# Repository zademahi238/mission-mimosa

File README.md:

# Mission Mimosa

### A Visuo-Tactile Manipulation System

*Giving robots a sense of touch.*

---

## Overview

**Mission Mimosa** explores **visuo-tactile manipulation** on the **SO-101 robotic arm**, combining visual observations with tactile sensing for robot manipulation.

The main objective is to investigate:

> **Does tactile information improve robot manipulation performance?**

To answer this, we compare **task-completion success rates with and without tactile sensing** across different robot-learning policies.

---

## Components

### SO-101

The **SO-101** robotic arm is used as the primary platform for collecting demonstrations and evaluating learned manipulation policies.

### FlexiTac

**FlexiTac** provides the tactile sensing hardware used to capture contact information during manipulation.

→ [`flexitac/`](./flexitac)

### LeFlexiTac

**LeFlexiTac** integrates tactile sensing with the **LeRobot** framework, enabling tactile observations to be incorporated into robot-learning workflows.

→ [`leflexitac/`](./leflexitac)

### LeRobot

**LeRobot** provides the robotics framework used for data collection, policy training, and deployment on the SO-101.

→ [`lerobot/`](./lerobot)

---

## Policies

Mission Mimosa explores multiple approaches for learning robot manipulation:

* **[ACT](./docs/policies/act.md)** — Action Chunking with Transformers for learning robot actions from demonstrations.

* **[B-Spline Policy](./docs/imitation-learning/bspline_policy_updated.md)** — Represents robot actions as smooth, continuous trajectories for manipulation.

* **[Diffusion Policy](./docs/policies/diffusion.md)** — Uses diffusion-based action generation for visuomotor control.

* **[SmolVLA](https://huggingface.co/blog/smolvla)** — A compact Vision-Language-Action model designed for efficient real-world robotic manipulation. SmolVLA-450M combines a vision-language model with a flow-matching action expert and is designed to run on relatively affordable hardware, including the SO-101.

Comparing these policies allows us to study how different learning approaches perform with visual information alone and when tactile information is introduced.

---

## Experiment

The core experiment compares two observation settings:

| Setup                | Vision | Tactile |
| :------------------- | :----: | :-----: |
| **Vision Only**      |    ✓   |    —    |
| **Vision + Tactile** |    ✓   |    ✓    |

Each setup is evaluated using **task-completion success rate** across manipulation tasks and different learning policies.

```chart Success Rate Comparison
[
  {
    "label": "ACT",
    "bars": [
      { "label": "50 eps", "value": 80, "series": "Vision" },
      { "label": "50 eps", "value": 90, "series": "Vision + Tactile" },
      { "label": "20 eps", "value": 50, "series": "Vision + Tactile" }
    ]
  },
  {
    "label": "SmolVLA",
    "bars": [
      { "label": "50 eps", "value": 70, "series": "Vision" },
      { "label": "20 eps", "value": 30, "series": "Vision" },
      { "label": "50 eps", "value": 50, "series": "Vision + Tactile" },
      { "label": "20 eps", "value": 70, "series": "Vision + Tactile" }
    ]
  }
]
```

This comparison helps isolate the contribution of tactile sensing and determine whether contact information leads to more reliable manipulation.

---

## Research Areas

Mission Mimosa focuses on the intersection of:

**Computer Vision · Tactile Sensing · Robot Learning · Robotic Manipulation**

The broader goal is to understand how robots can combine **visual and tactile information** to make better decisions during physical interaction.

---

## Repository Structure

```text
mission-mimosa/
│
├── assets/                  # Project media and visual assets
├── docs/                    # Documentation and research notes
│
├── flexitac/                # FlexiTac tactile sensing
├── leflexitac/              # LeRobot + tactile integration
├── lerobot/                 # Robot learning framework
├── bspline/                 # B-Spline policy
│
└── README.md
```

---

### Mission Mimosa

**Vision provides sight.
Tactile sensing provides touch.**

*Mission Mimosa explores how combining both can improve robotic manipulation.*

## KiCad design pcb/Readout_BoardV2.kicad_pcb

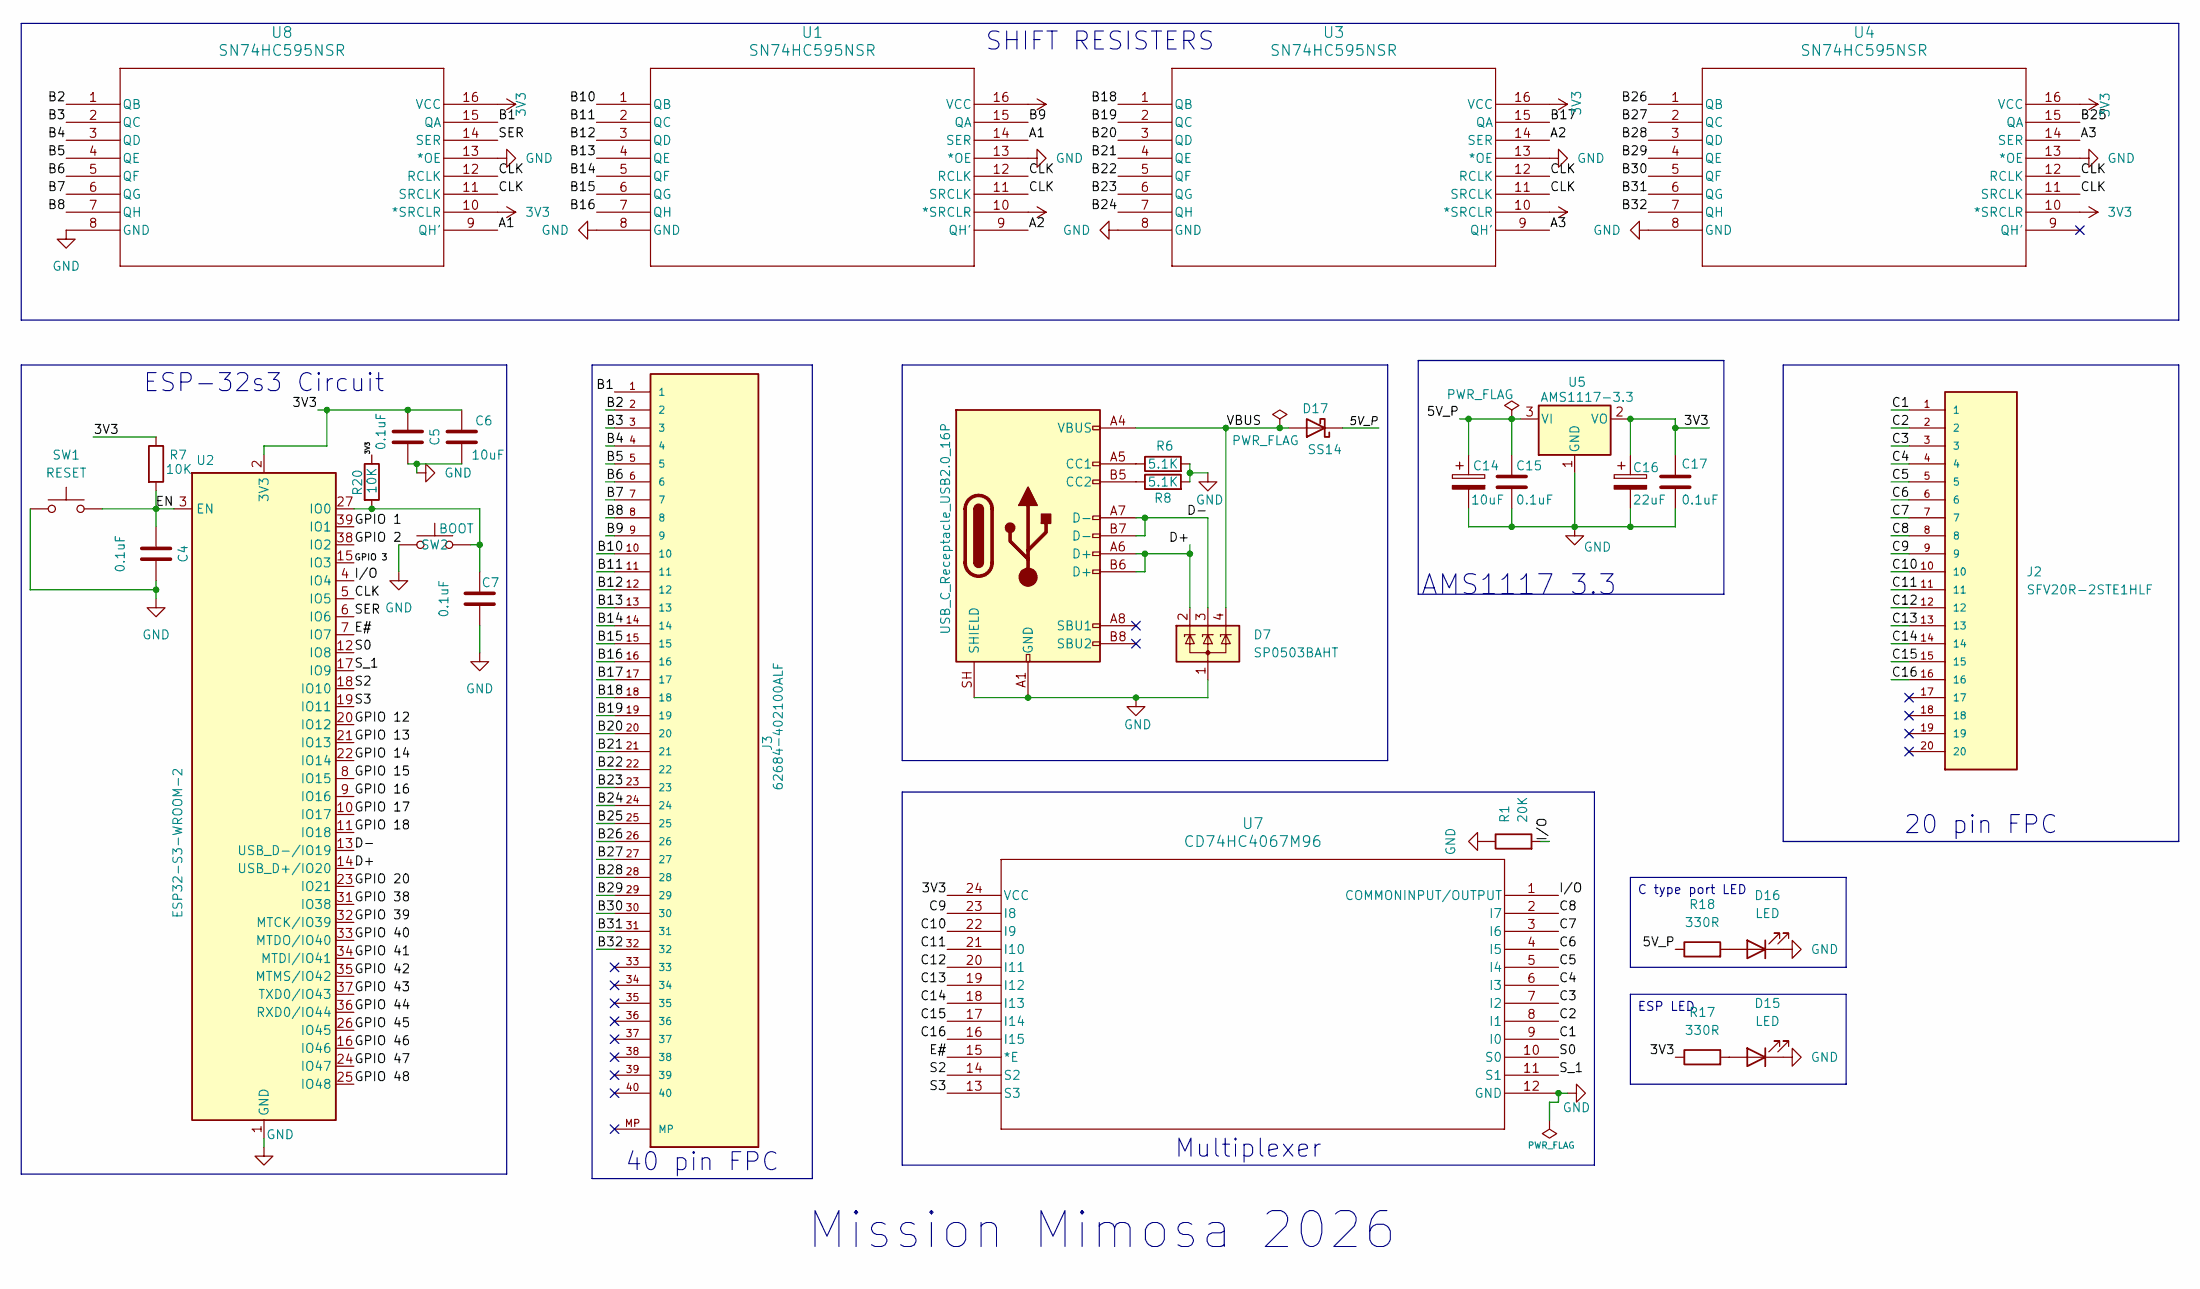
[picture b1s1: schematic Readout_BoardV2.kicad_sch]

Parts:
C4, C5, C7, C15, C17: 0.1uF; C_0805_2012Metric
C6, C14: 10uF; C_0805_2012Metric
C16: 22uF; C_0805_2012Metric
D7: SP0503BAHT; SOT-143
D15, D16: LED; LED_0805_2012Metric
D17: SS14; D_SMA
J2: SFV20R-2STE1HLF; Hirose_FH12-20S-0.5SH_1x20-1MP_P0.50mm_Horizontal; PARTREV C
J3: 62684-402100ALF; Hirose_FH12-40S-0.5SH_1x40-1MP_P0.50mm_Horizontal; PARTREV AK
J5: USB_C_Receptacle_USB2.0_16P; USB_C_Receptacle_GCT_USB4105-xx-A_16P_TopMnt_Horizontal
R1: 20K; R_0805_2012Metric
R6, R8: 5.1K; R_0805_2012Metric
R7, R20: 10K; R_0805_2012Metric
R17, R18: 330R; R_0805_2012Metric
SW1: RESET; SW_Push_SPST_NO_Alps_SKRK
SW2: BOOT; SW_Push_SPST_NO_Alps_SKRK
U1, U3, U4, U8: SN74HC595NSR; NS16
U2: ESP32-S3-WROOM-2; ESP32-S3-WROOM-1
U5: AMS1117-3.3; SOT-223-3_TabPin2
U7: CD74HC4067M96; DW24

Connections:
3V3: C5.2, C6.1, C16.1, C17.1, R7.1, R17.1, R20.1, U1.10 (*SRCLR), U1.16 (VCC), U2.2 (3V3), U3.10 (*SRCLR), U3.16 (VCC), U4.10 (*SRCLR), U4.16 (VCC), U5.2 (VO), U7.24 (VCC), U8.10 (*SRCLR), U8.16 (VCC)
/5V_P: C14.1, C15.1, D17.1 (K), R18.1, U5.3 (VI)
/A1: U1.14 (SER), U8.9 (QH')
/A2: U1.9 (QH'), U3.14 (SER)
/A3: U3.9 (QH'), U4.14 (SER)
/B1: J3.1, U8.15 (QA)
/B2: J3.2, U8.1 (QB)
/B3: J3.3, U8.2 (QC)
/B4: J3.4, U8.3 (QD)
/B5: J3.5, U8.4 (QE)
/B6: J3.6, U8.5 (QF)
/B7: J3.7, U8.6 (QG)
/B8: J3.8, U8.7 (QH)
/B9: J3.9, U1.15 (QA)
/B10: J3.10, U1.1 (QB)
/B11: J3.11, U1.2 (QC)
/B12: J3.12, U1.3 (QD)
/B13: J3.13, U1.4 (QE)
/B14: J3.14, U1.5 (QF)
/B15: J3.15, U1.6 (QG)
/B16: J3.16, U1.7 (QH)
/B17: J3.17, U3.15 (QA)
/B18: J3.18, U3.1 (QB)
/B19: J3.19, U3.2 (QC)
/B20: J3.20, U3.3 (QD)
/B21: J3.21, U3.4 (QE)
/B22: J3.22, U3.5 (QF)
/B23: J3.23, U3.6 (QG)
/B24: J3.24, U3.7 (QH)
/B25: J3.25, U4.15 (QA)
/B26: J3.26, U4.1 (QB)
/B27: J3.27, U4.2 (QC)
/B28: J3.28, U4.3 (QD)
/B29: J3.29, U4.4 (QE)
/B30: J3.30, U4.5 (QF)
/B31: J3.31, U4.6 (QG)
/B32: J3.32, U4.7 (QH)
/C1: J2.1, U7.9 (I0)
/C2: J2.2, U7.8 (I1)
/C3: J2.3, U7.7 (I2)
/C4: J2.4, U7.6 (I3)
/C5: J2.5, U7.5 (I4)
/C6: J2.6, U7.4 (I5)
/C7: J2.7, U7.3 (I6)
/C8: J2.8, U7.2 (I7)
/C9: J2.9, U7.23 (I8)
/C10: J2.10, U7.22 (I9)
/C11: J2.11, U7.21 (I10)
/C12: J2.12, U7.20 (I11)
/C13: J2.13, U7.19 (I12)
/C14: J2.14, U7.18 (I13)
/C15: J2.15, U7.17 (I14)
/C16: J2.16, U7.16 (I15)
/CLK: U1.11 (SRCLK), U1.12 (RCLK), U2.5 (IO5), U3.11 (SRCLK), U3.12 (RCLK), U4.11 (SRCLK), U4.12 (RCLK), U8.11 (SRCLK), U8.12 (RCLK)
/D+: D7.2 (K), J5.A6 (D+), J5.B6 (D+), U2.14 (USB_D+/IO20)
/D-: D7.3 (K), J5.A7 (D-), J5.B7 (D-), U2.13 (USB_D-/IO19)
/E#: U2.7 (IO7), U7.15 (*E)
/EN: C4.2, R7.2, SW1.2, U2.3 (EN)
/GPIO 1: U2.39 (IO1)
/GPIO 2: U2.38 (IO2)
/GPIO 3: U2.15 (IO3)
/GPIO 12: U2.20 (IO12)
/GPIO 13: U2.21 (IO13)
/GPIO 14: U2.22 (IO14)
/GPIO 15: U2.8 (IO15)
/GPIO 16: U2.9 (IO16)
/GPIO 17: U2.10 (IO17)
/GPIO 18: U2.11 (IO18)
/GPIO 20: U2.23 (IO21)
/GPIO 38: U2.31 (IO38)
/GPIO 39: U2.32 (MTCK/IO39)
/GPIO 40: U2.33 (MTDO/IO40)
/GPIO 41: U2.34 (MTDI/IO41)
/GPIO 42: U2.35 (MTMS/IO42)
/GPIO 43: U2.37 (TXD0/IO43)
/GPIO 44: U2.36 (RXD0/IO44)
/GPIO 45: U2.26 (IO45)
/GPIO 46: U2.16 (IO46)
/GPIO 47: U2.24 (IO47)
/GPIO 48: U2.25 (IO48)
/I/O: R1.2, U2.4 (IO4), U7.1 (COMMONINPUT/OUTPUT)
/S0: U2.12 (IO8), U7.10 (S0)
/S2: U2.18 (IO10), U7.14 (S2)
/S3: U2.19 (IO11), U7.13 (S3)
/SER: U2.6 (IO6), U8.14 (SER)
/S_1: U2.17 (IO9), U7.11 (S1)
/VBUS: D7.4 (K), D17.2 (A), J5.A4 (VBUS), J5.A9 (VBUS), J5.B4 (VBUS), J5.B9 (VBUS)
GND: C4.1, C5.1, C6.2, C7.1, C14.2, C15.2, C16.2, C17.2, D7.1 (A), D15.1 (K), D16.1 (K), J5.A1 (GND), J5.A12 (GND), J5.B1 (GND), J5.B12 (GND), J5.SH (SHIELD), R1.1, R6.2, R8.2, SW1.1, SW2.1, U1.8 (GND), U1.13 (*OE), U2.1 (GND), U2.40 (GND), U2.41 (GND), U3.8 (GND), U3.13 (*OE), U4.8 (GND), U4.13 (*OE), U5.1 (GND), U7.12 (GND), U8.8 (GND), U8.13 (*OE)
unnamed: D15.2 (A), R17.2
unnamed: D16.2 (A), R18.2
unnamed: J5.A5 (CC1), R6.1
unnamed: J5.B5 (CC2), R8.1
unnamed: C7.2, R20.2, SW2.2, U2.27 (IO0)

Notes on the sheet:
Mission Mimosa 2026
AMS1117 3.3
ESP LED
C type port LED
ESP-32s3 Circuit
20 pin FPC
Multiplexer
SHIFT RESISTERS
40 pin FPC

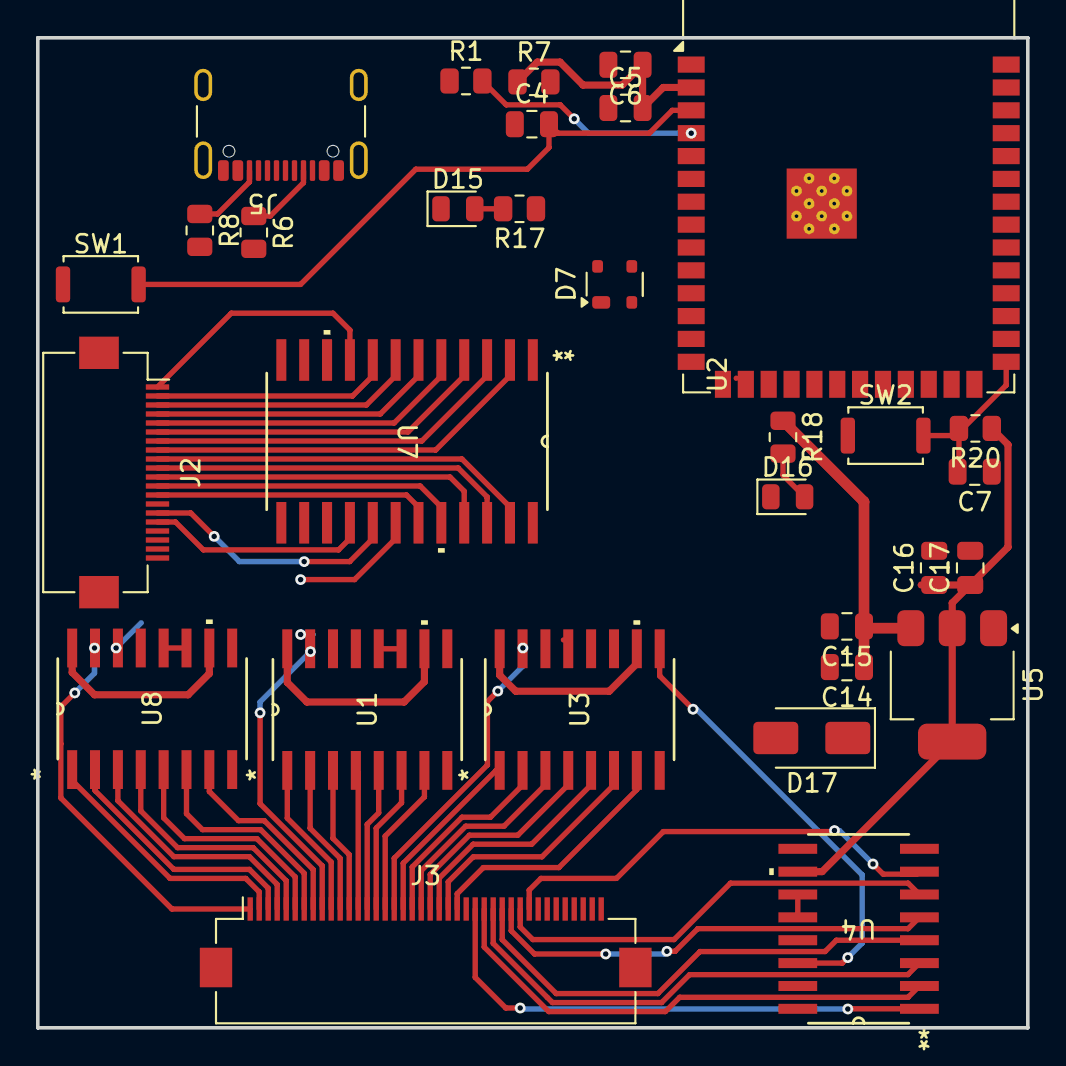
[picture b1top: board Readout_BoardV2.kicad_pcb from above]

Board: 2 copper layers, 55.0 x 55.0 mm, 31 parts (0 on the bottom side), 71 nets.
